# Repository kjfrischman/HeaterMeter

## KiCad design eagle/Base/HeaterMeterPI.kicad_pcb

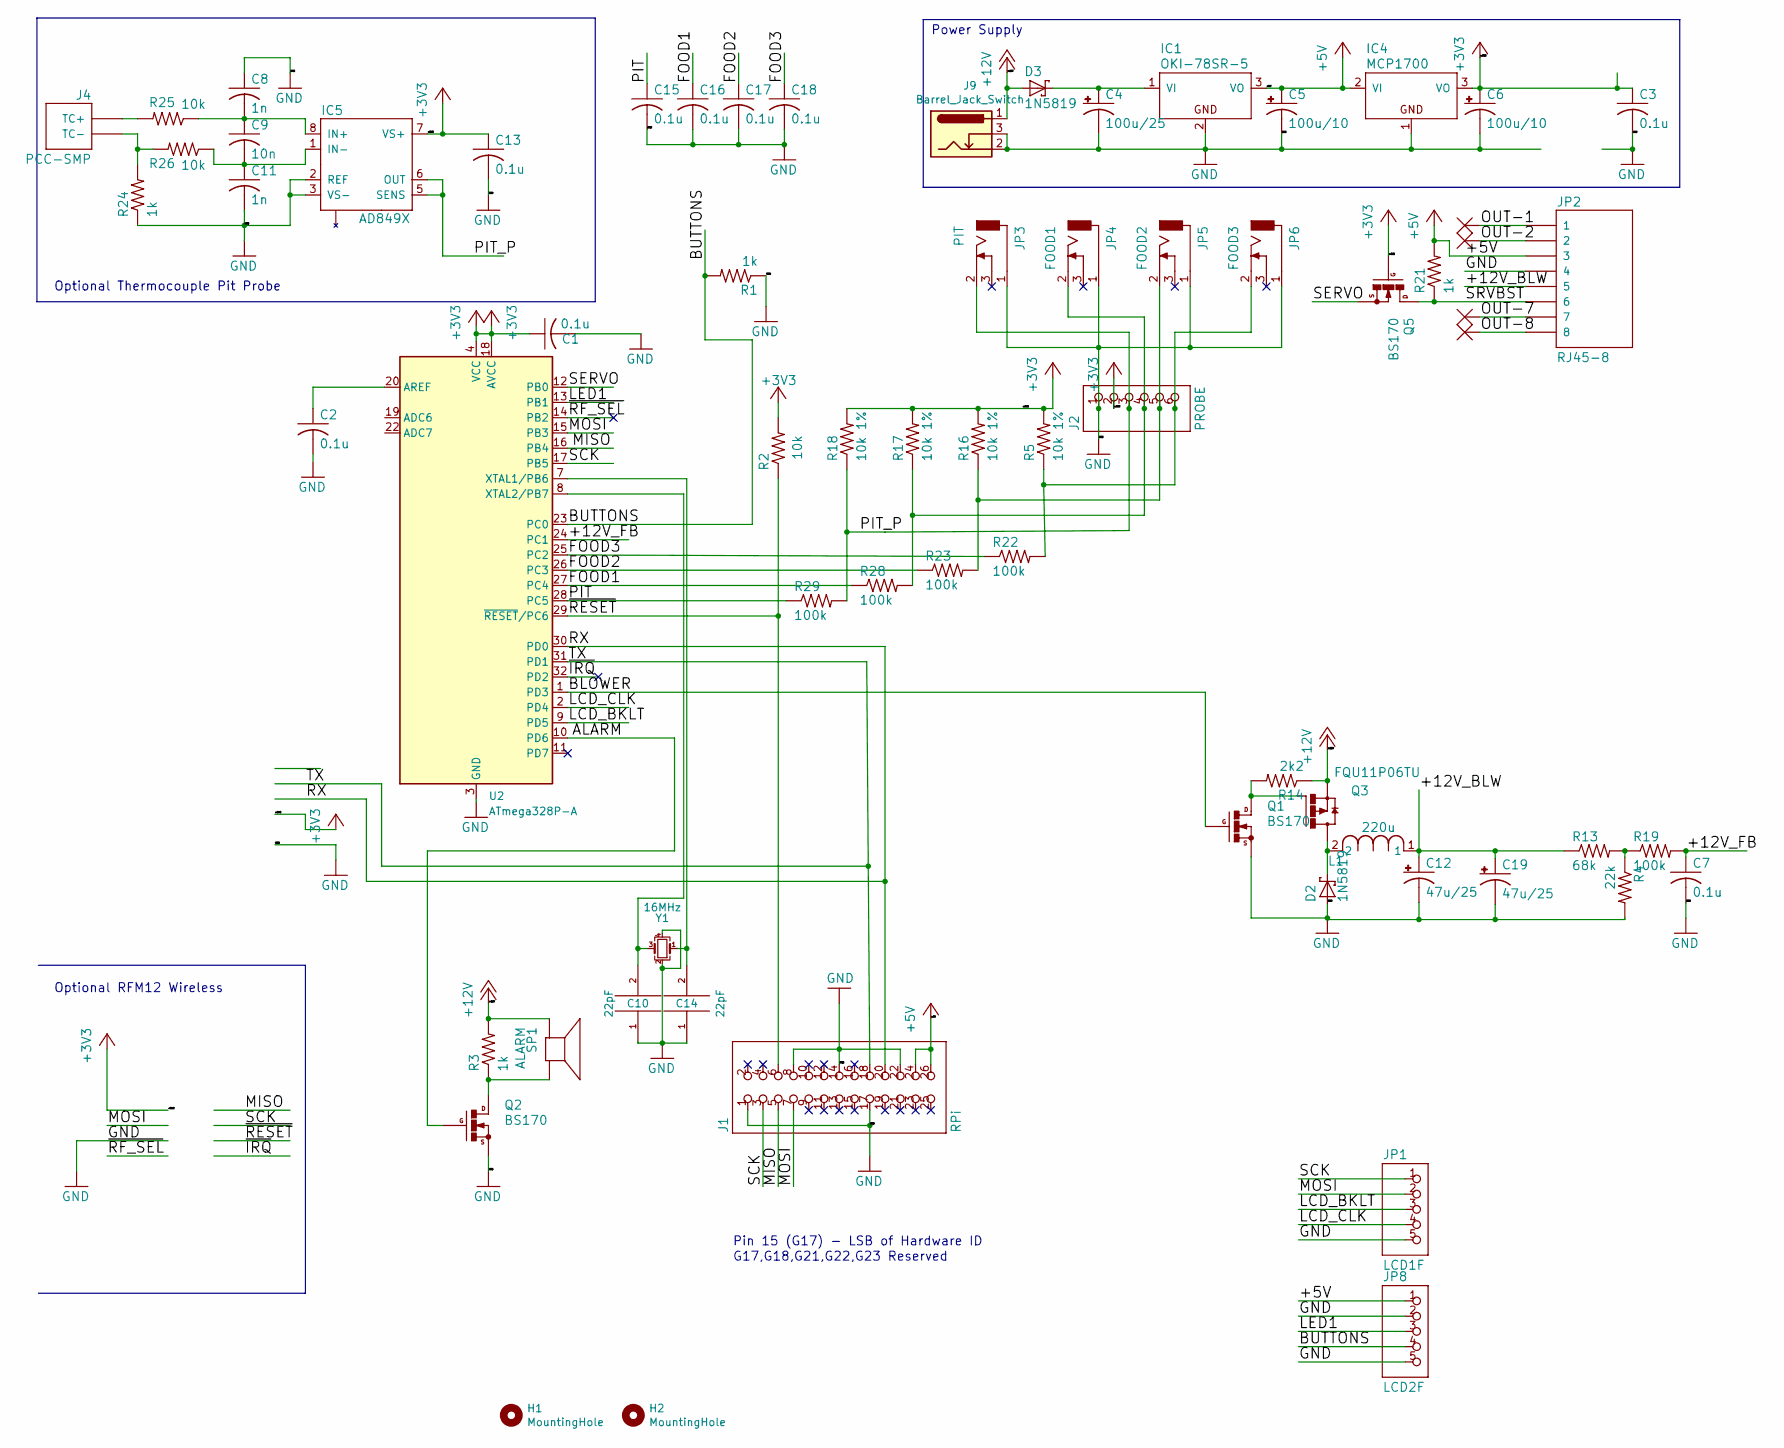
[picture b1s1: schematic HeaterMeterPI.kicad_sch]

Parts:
C1, C2, C3: 0.1u; C_0603_1608Metric_Pad1.08x0.95mm_HandSolder
C4: 100u/25; E2,5-6
C5, C6: 100u/10; E2,5-5
C7, C15, C16, C17, C18: 0.1u; C025-025X050
C8, C11: 1n; C0805
C9: 10n; C0805
C10, C14: 22pF; C_0402_1005Metric_Pad0.74x0.62mm_HandSolder
C12, C19: 47u/25; E2,5-5
C13: 0.1u; C0805
D2: 1N5819; D_DO-201AD_P12.70mm_Horizontal
D3: 1N5819; DO41-7
H1, H2: MountingHole; MountingHole_3.2mm_M3_ISO14580
IC1: OKI-78SR-5; TO220HMURATA
IC4: MCP1700; TO92
IC5: AD849X; MSOP8
J1: RPi; 2X13
J2: PROBE; 1X06
J4: PCC-SMP
J9: Barrel_Jack_Switch; BarrelJack_Horizontal
JP1: LCD1F; 1X05
JP2: RJ45-8; RJ45-8-1H
JP3: PIT; CUI-MJ1-2503A
JP4: FOOD1; CUI-MJ1-2503A
JP5: FOOD2; CUI-MJ1-2503A
JP6: FOOD3; CUI-MJ1-2503A
JP8: LCD2F; 1X05
L1: 220u; MSS1278T
Q1, Q2, Q5: BS170; SOT54E
Q3: FQU11P06TU; TO251
R1, R3, R21, R24: 1k; R_0603_1608Metric_Pad0.98x0.95mm_HandSolder
R2, R25, R26: 10k; R_0603_1608Metric_Pad0.98x0.95mm_HandSolder
R4: 22k; R_0603_1608Metric_Pad0.98x0.95mm_HandSolder
R5, R16, R17, R18: 10k 1%; R_0603_1608Metric_Pad0.98x0.95mm_HandSolder
R13: 68k; R_0603_1608Metric_Pad0.98x0.95mm_HandSolder
R14: 2k2; R_0603_1608Metric_Pad0.98x0.95mm_HandSolder
R19, R22, R23, R28, R29: 100k; R_0603_1608Metric_Pad0.98x0.95mm_HandSolder
SP1: ALARM; AL11P
U2: ATmega328P-A; TQFP-32_7x7mm_P0.8mm
U$1, U$2, U$3, U$4: THROUGH-HOLE; PAD-032
Y1: 16MHz; Crystal_SMD_3225-4Pin_3.2x2.5mm

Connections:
+3V3: C1.1, C3.1, C6.+, C13.1, IC4.3 (VO), IC5.7 (VS+), J2.2, Q5.G, R2.2, R5.2, R16.2, R17.2, R18.2, U2.4 (VCC), U2.6 (VCC), U2.18 (AVCC)
+5V: C5.+, IC1.3 (VO), IC4.2 (VI), J1.24, J1.26, JP2.3, JP8.1, R21.2
+12V: D3.A, J9.1, Q3.3 (S), R3.2, R14.1, SP1.+
/+12V_BLW: C12.+, C19.+, JP2.5, L1.1, R13.1
/+12V_FB: C7.1, R19.2, U2.24 (PC1)
/ALARM: Q2.G, U2.10 (PD6)
/BLOWER: Q1.G, U2.1 (PD3)
/BUTTONS: JP8.4, R1.2, U2.23 (PC0)
/FOOD1: C16.1, R28.1, U2.27 (PC4)
/FOOD2: C17.1, R23.1, U2.26 (PC3)
/FOOD3: C18.1, R22.1, U2.25 (PC2)
/LCD_BKLT: JP1.3, U2.9 (PD5)
/LCD_CLK: JP1.4, U2.2 (PD4)
/LED1: JP8.3, U2.13 (PB1)
/MISO: J1.5, U2.16 (PB4)
/MOSI: J1.7, JP1.2, U2.15 (PB3)
/OUT-1: JP2.1, U$3.P
/OUT-2: JP2.2, U$4.P
/OUT-7: JP2.7, U$2.P
/OUT-8: JP2.8, U$1.P
/PIT: C15.1, R29.1, U2.28 (PC5)
/PIT_P: IC5.5 (SENS), IC5.6 (OUT), J2.3, JP3.2, R18.1, R29.2
/RX: J1.20, U2.30 (PD0)
/SCK: J1.3, JP1.1, U2.17 (PB5)
/SERVO: Q5.S, U2.12 (PB0)
/SRVBST: JP2.6, Q5.D, R21.1
/TX: J1.18, U2.31 (PD1)
/~IRQ: U2.32 (PD2)
/~RESET: J1.6, R2.1, U2.29 (~RESET/PC6)
/~RF_SEL: U2.14 (PB2)
GND: C1.2, C2.2, C3.2, C4.-, C5.-, C6.-, C7.2, C8.1, C10.1, C11.2, C12.-, C13.2, C14.1, C15.2, C16.2, C17.2, C18.2, C19.-, D2.A, IC1.2 (GND), IC4.1 (GND), IC5.2 (REF), IC5.3 (VS-), J1.1, J1.8, J1.14, J1.17, J1.22, J2.1, J9.2, J9.3, JP1.5, JP2.4, JP3.1, JP4.1, JP5.1, JP6.1, JP8.2, JP8.5, Q1.S, Q2.S, R1.1, R4.2, R24.1, U2.3 (GND), U2.5 (GND), U2.21 (GND), Y1.2, Y1.4
unnamed: D2.C, L1.2, Q3.2@1 (D), Q3.2@2 (D)
unnamed: C4.+, D3.C, IC1.1 (VI)
unnamed: C8.2, C9.1, IC5.8 (IN+), R25.1
unnamed: C9.2, C11.1, IC5.1 (IN-), R26.1
unnamed: J2.4, JP4.2, R17.1, R28.2
unnamed: J2.5, JP5.2, R16.1, R23.2
unnamed: J2.6, JP6.2, R5.1, R22.2
unnamed: J4.TC+, R25.2
unnamed: J4.TC-, R24.2, R26.2
unnamed: Q2.D, R3.1, SP1.-
unnamed: Q1.D, Q3.1 (G), R14.2
unnamed: R4.1, R13.2, R19.1
unnamed: C2.1, U2.20 (AREF)
unnamed: C14.2, U2.7 (XTAL1/PB6), Y1.1
unnamed: C10.2, U2.8 (XTAL2/PB7), Y1.3

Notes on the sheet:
Optional RFM12 Wireless
Optional Thermocouple Pit Probe
Pin 15 (G17) - LSB of Hardware ID
Power Supply
G17,G18,G21,G22,G23 Reserved

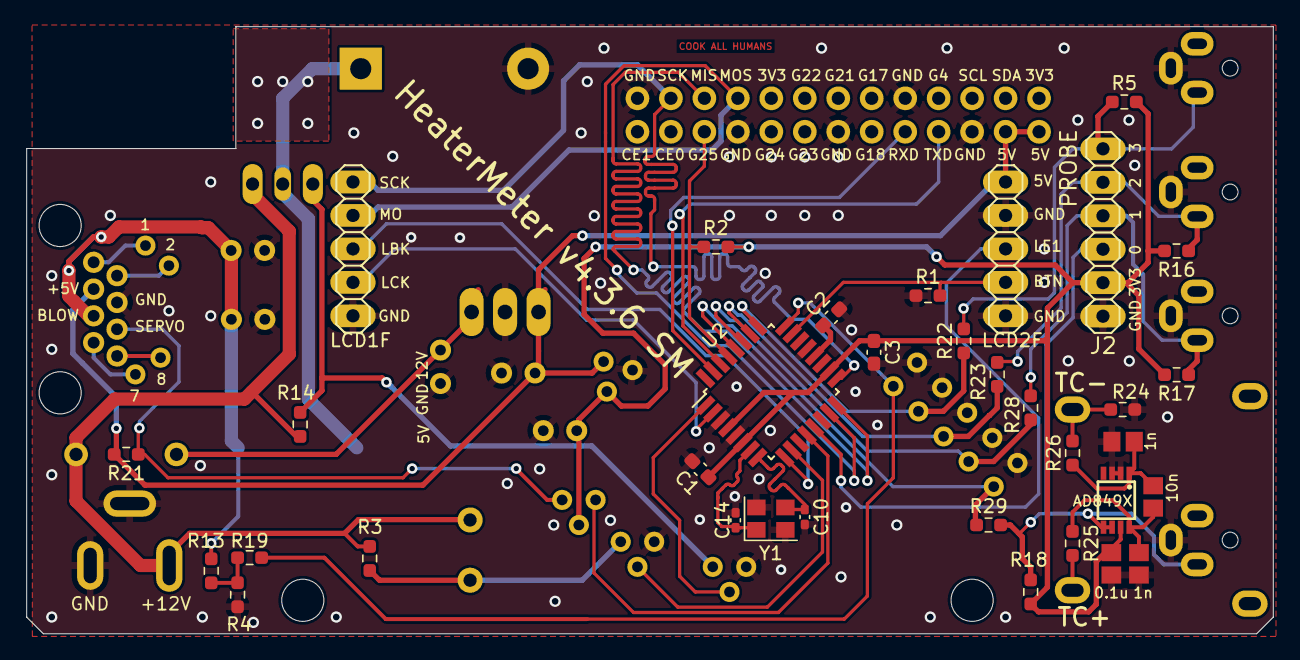
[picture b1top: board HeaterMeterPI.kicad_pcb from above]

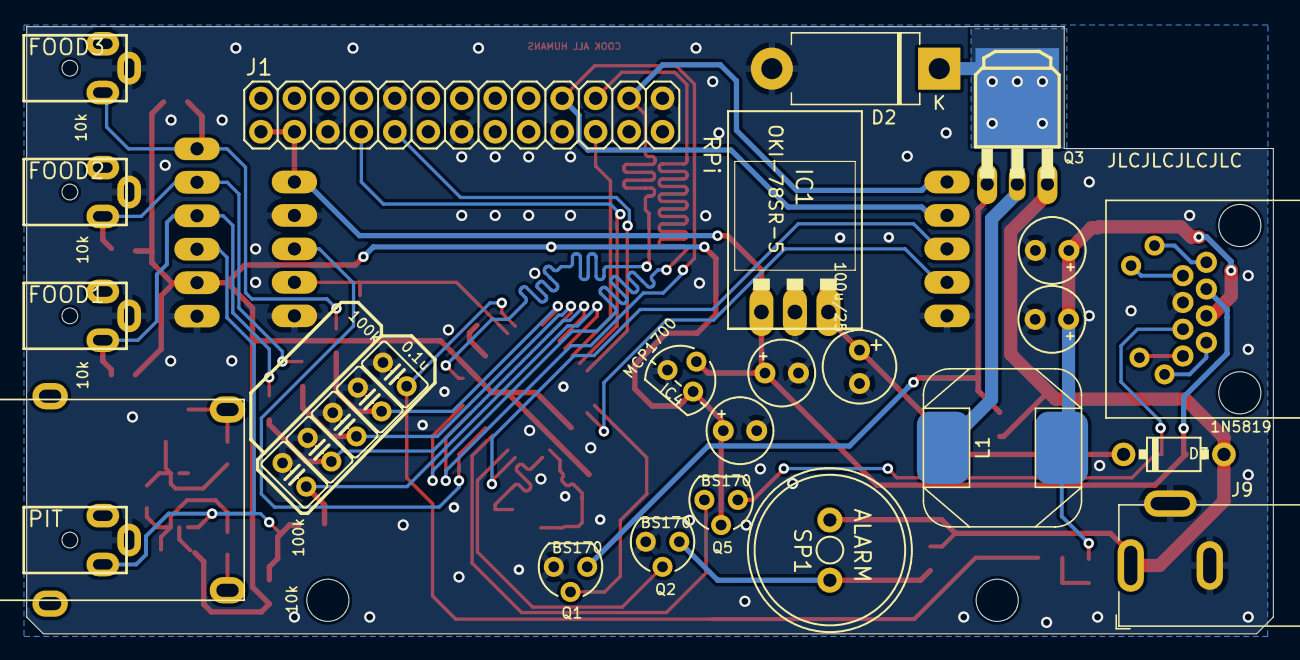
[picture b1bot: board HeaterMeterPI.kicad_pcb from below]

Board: 2 copper layers, 94.6 x 46.1 mm, 68 parts (28 on the bottom side), 44 nets.

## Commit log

2024-03-10 [eagle] Upgraded to KiCad 8.0. Moved to 2.5A fan drive solution.
